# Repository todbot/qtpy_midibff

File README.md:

# qtpy_midibff

QTPy MIDI BFF — a small MIDI interface board for QTPy / Xiao class boards (RP2040 or compatible).
The board breaks out the host MCU's hardware UART to standard MIDI IN and MIDI OUT jacks (TRS or 5-pin DIN).

## Hardware

The PCB is meant for easy assembly using only through-hole components. 
It is essentialy a QTPy "doubler" with a standard MIDI In and MIDI Out circuit, 
with a 4-pin I2C header for a standard OLED display (usually 128x32 SSD1306).

## Assembling

_Coming soon._

## Arduino sketches

Requires [arduino-pico](https://arduino-pico.readthedocs.io/en/latest/install.html) board core.

Set **Tools > USB Stack: Adafruit TinyUSB** before uploading any sketch.

Libraries needed (Arduino Library Manager):
- [Adafruit TinyUSB](https://github.com/adafruit/Adafruit_TinyUSB_Arduino)
- [MIDI Library](https://github.com/FortySevenEffects/arduino_midi_library)
- [Adafruit SSD1306](https://github.com/adafruit/Adafruit_SSD1306) + [Adafruit GFX Library](https://github.com/adafruit/Adafruit-GFX-Library) _(OLED sketches only)_
- [Adafruit SPIFlash](https://github.com/adafruit/Adafruit_SPIFlash) + [SdFat - Adafruit Fork](https://github.com/adafruit/SdFat) + [ArduinoJson](https://arduinojson.org) _(MSC sketch only)_

### `midi_interface` — USB-MIDI ↔ UART-MIDI bridge

[`arduino/midi_interface/`](arduino/midi_interface/)

Forwards all MIDI between USB and UART in both directions. Includes scaffolding to filter or
transform messages — uncomment the examples or add your own:

- Drop realtime messages (clock, active sensing, etc.)
- Transpose notes on a channel
- Remap channels

```
arduino-cli compile \
  --fqbn rp2040:rp2040:adafruit_qtpy:usbstack=tinyusb \
  arduino/midi_interface
```

SysEx messages up to 127 bytes are forwarded. See the source for notes on larger SysEx.

### `midi_interface_oled` — bridge with OLED display

[`arduino/midi_interface_oled/`](arduino/midi_interface_oled/)

Same bridge as `midi_interface`, with a 128x32 SSD1306 I2C OLED that displays each incoming
message. Realtime messages (clock, active sensing) are forwarded but not shown, to avoid flicker.

```
arduino-cli compile \
  --fqbn rp2040:rp2040:adafruit_qtpy:usbstack=tinyusb \
  arduino/midi_interface_oled
```

### `midi_interface_msc` — bridge with USB flash drive and config file

[`arduino/midi_interface_msc/`](arduino/midi_interface_msc/)

Extends `midi_interface_oled` with a USB Mass Storage device backed by the RP2040's internal
flash (the filesystem partition). The drive contains a `config.json` file that controls runtime
behaviour — no recompile needed to change settings.

```json
{
  "name": "MIDI BFF",
  "manufacturer": "todbot",
  "filter_realtime": false,
  "transpose": 0
}
```

Edit `config.json` on the drive, eject it, then reset the board to apply the new settings.
The `filter_realtime` and `transpose` fields are applied in both directions.

Requires a board Flash Size setting that includes a 1MB filesystem partition. Compile commands for each supported board:

```
# QTPy RP2040 (8MB flash)
arduino-cli compile \
  --fqbn rp2040:rp2040:adafruit_qtpy:usbstack=tinyusb,flash=8388608_1048576 \
  arduino/midi_interface_msc

# Xiao RP2040 (2MB flash)
arduino-cli compile \
  --fqbn rp2040:rp2040:seeed_xiao_rp2040:usbstack=tinyusb,flash=2097152_1048576 \
  arduino/midi_interface_msc
```

### `midi_interface_simple` — simplified bridge for learners

[`arduino/midi_interface_simple/`](arduino/midi_interface_simple/)

Same USB-MIDI ↔ UART-MIDI bridge with the same filter/transform scaffolding, but with SysEx
handling and advanced notes removed. A good starting point if you just want to read and modify
the forwarding logic without the extra complexity.

```
arduino-cli compile \
  --fqbn rp2040:rp2040:adafruit_qtpy:usbstack=tinyusb \
  arduino/midi_interface_simple
```

## CircuitPython sketches

Requires CircuitPython 9+ firmware on the board.

Libraries needed:
- [tmidi](https://github.com/todbot/CircuitPython_TMIDI) — copy `tmidi.py` to `/lib/` on your device or install with `circup tmidi`
- [adafruit_ssd1306](https://github.com/adafruit/Adafruit_CircuitPython_SSD1306) — install with `circup install adafruit_ssd1306` _(OLED sketches only)_

### `midi_interface` — USB-MIDI ↔ UART-MIDI bridge

[`circuitpython/midi_interface/`](circuitpython/midi_interface/)

Forwards all MIDI between USB and UART in both directions. Same filter/transform scaffolding
as the Arduino version — uncomment the examples or add your own:

- Drop realtime messages (clock, active sensing, etc.)
- Transpose notes on a channel
- Remap channels

SysEx messages up to 127 bytes are forwarded. Increase the `sysex_buf_*` bytearray sizes in
the source to raise the limit.

Copy `code.py` to the root of your device, or copy the whole `midi_interface/` folder and
rename `code.py` to suit.

### `midi_interface_oled` — bridge with OLED display

[`circuitpython/midi_interface_oled/`](circuitpython/midi_interface_oled/)

Same bridge as `midi_interface`, with a 128x32 SSD1306 I2C OLED that displays each incoming
message. Realtime messages are forwarded but not shown, to avoid flicker. The sketch continues
as a plain MIDI bridge if no display is connected.

Copy `code.py` to the root of your device, or copy the whole `midi_interface_oled/` folder and
rename `code.py` to suit.

## Hardware

Schematic and PCB in `schematics/midi_bff/` (KiCad).

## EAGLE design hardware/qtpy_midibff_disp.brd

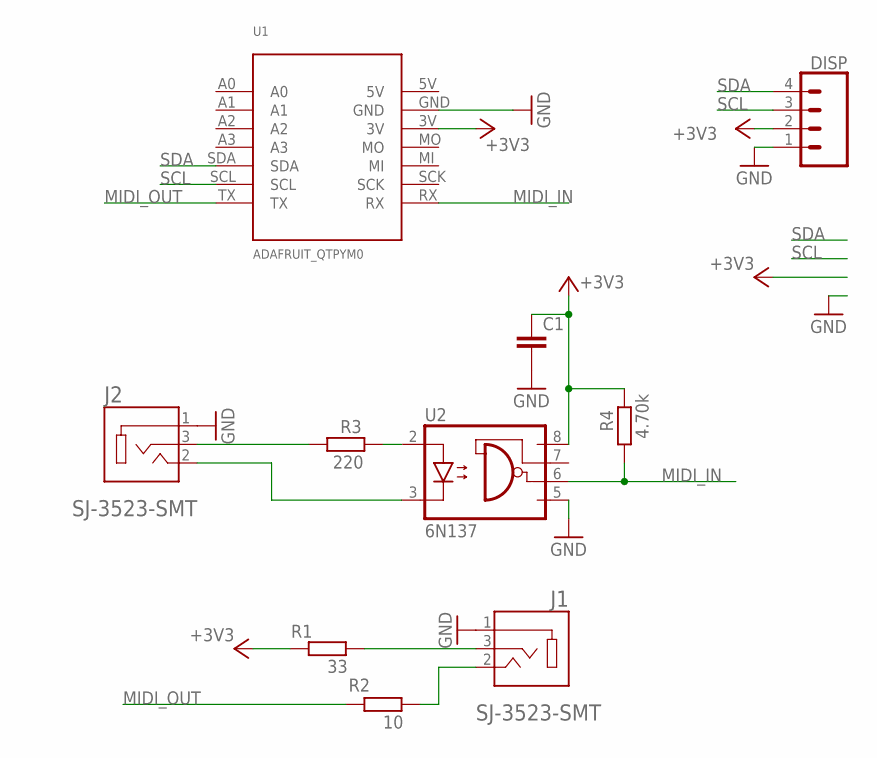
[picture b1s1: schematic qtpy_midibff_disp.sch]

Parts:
C1: C-EU025-025X050; C025-025X050
DISP: CONN_04; 1X04
J1, J2: SJ-3523-SMT; CUI_SJ-3523-SMT
R1: 33; 0204/7
R2: 10; 0204/7
R3: 220; 0204/7
R4: 4.70k; 0204/7
U1: ADAFRUIT_QTPYM0; ADAFRUIT_QTPY_M0
U2: 6N137; DIL08

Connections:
+3V3: C1.1, DISP.2, R1.2, R4.1, U1.3V, U2.8 (VCC)
GND: C1.2, DISP.1, J1.1, J2.1, U1.GND, U2.5 (GND)
MIDI_IN: R4.2, U1.RX, U2.6 (VO)
MIDI_OUT: R2.2, U1.TX
unnamed: J1.3, R1.1
unnamed: R3.1, U2.2 (A)
unnamed: J2.2, U2.3 (C)
unnamed: J2.3, R3.2
unnamed: J1.2, R2.1
SCL: DISP.3, U1.SCL
SDA: DISP.4, U1.SDA

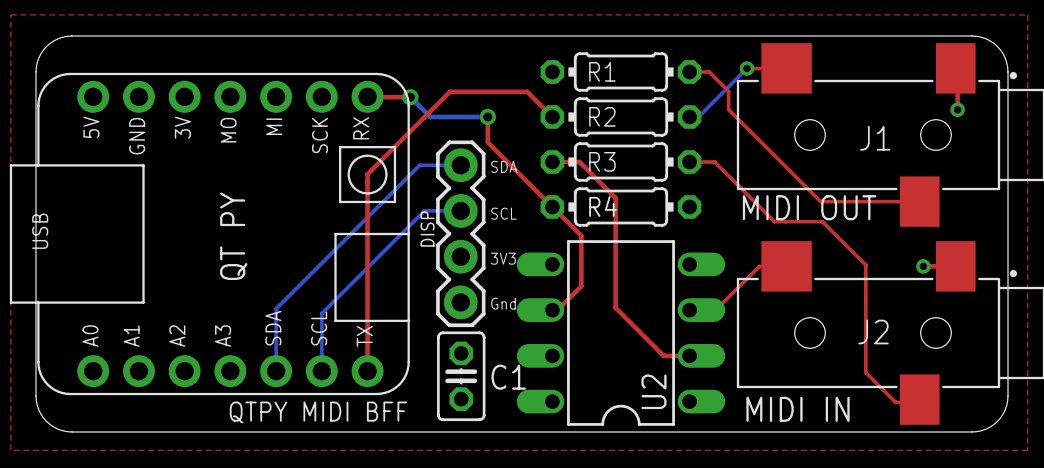
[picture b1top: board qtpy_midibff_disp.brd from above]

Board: 2 copper layers, 54.0 x 22.0 mm, 10 parts (0 on the bottom side), 11 nets.

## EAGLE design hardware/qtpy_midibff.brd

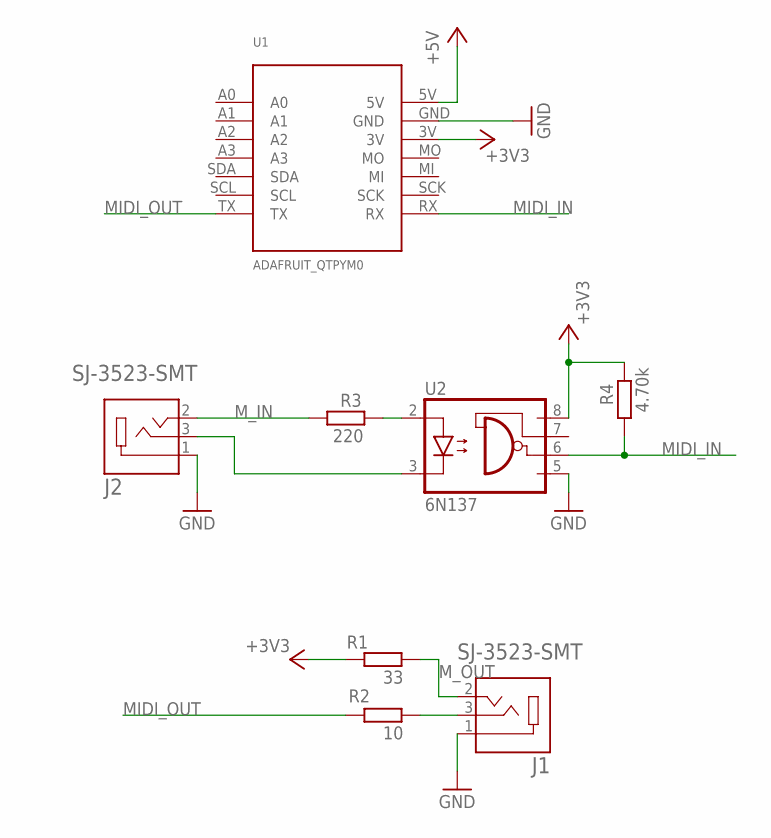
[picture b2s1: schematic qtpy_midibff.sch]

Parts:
J1, J2: SJ-3523-SMT; CUI_SJ-3523-SMT
R1: 33; 0204/7
R2: 10; 0204/7
R3: 220; 0204/7
R4: 4.70k; 0204/7
U1: ADAFRUIT_QTPYM0; ADAFRUIT_QTPY_M0
U2: 6N137; DIL08

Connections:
+3V3: R1.2, R4.1, U1.3V, U2.8 (VCC)
GND: J1.1, J2.1, U1.GND, U2.5 (GND)
MIDI_IN: R4.2, U1.RX, U2.6 (VO)
MIDI_OUT: R2.2, U1.TX
M_IN: J2.2, R3.2
M_OUT: J1.2, R1.1
unnamed: J1.3, R2.1
unnamed: R3.1, U2.2 (A)
unnamed: J2.3, U2.3 (C)
VLED: U1.5V

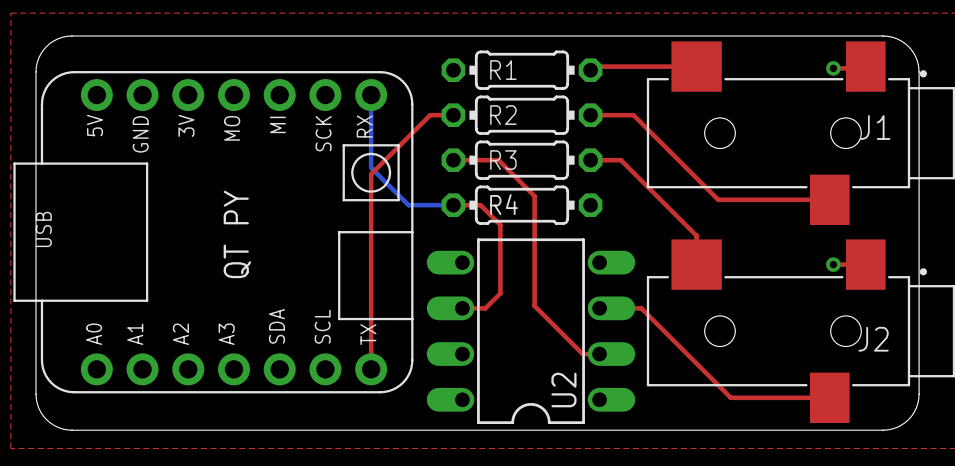
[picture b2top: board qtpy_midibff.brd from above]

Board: 2 copper layers, 49.1 x 21.9 mm, 8 parts (0 on the bottom side), 9 nets.

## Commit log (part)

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2022-07-31 sch brd
2022-08-01 added pic
2022-08-06 sigh trs-a/b will kill me
2026-05-10 new take on qtpy_midibff
2026-05-11 sent to production
2026-05-29 add first crack at arduino midi_interface
2026-05-29 new board img
2026-05-29 update gitignore
2026-05-29 update midi_interface to support sysex forwarding sorta, make midi_interface_simple that does not
2026-05-29 add circuitpython version of midi_interface
2026-05-30 add midi_interface_oled.ino
2026-05-30 add midi_interface_oled
2026-06-03 add midi_interface_msc. required making a custom FAT12 formatter
2026-06-11 resize to sch to A5
2026-06-12 add LED status to all Arduino sketches

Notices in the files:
parts and their libraries:
SparkFun-Connectors: Licensing: Creative Commons ShareAlike 4.0 International - https://creativecommons.org/licenses/by-sa/4.0
